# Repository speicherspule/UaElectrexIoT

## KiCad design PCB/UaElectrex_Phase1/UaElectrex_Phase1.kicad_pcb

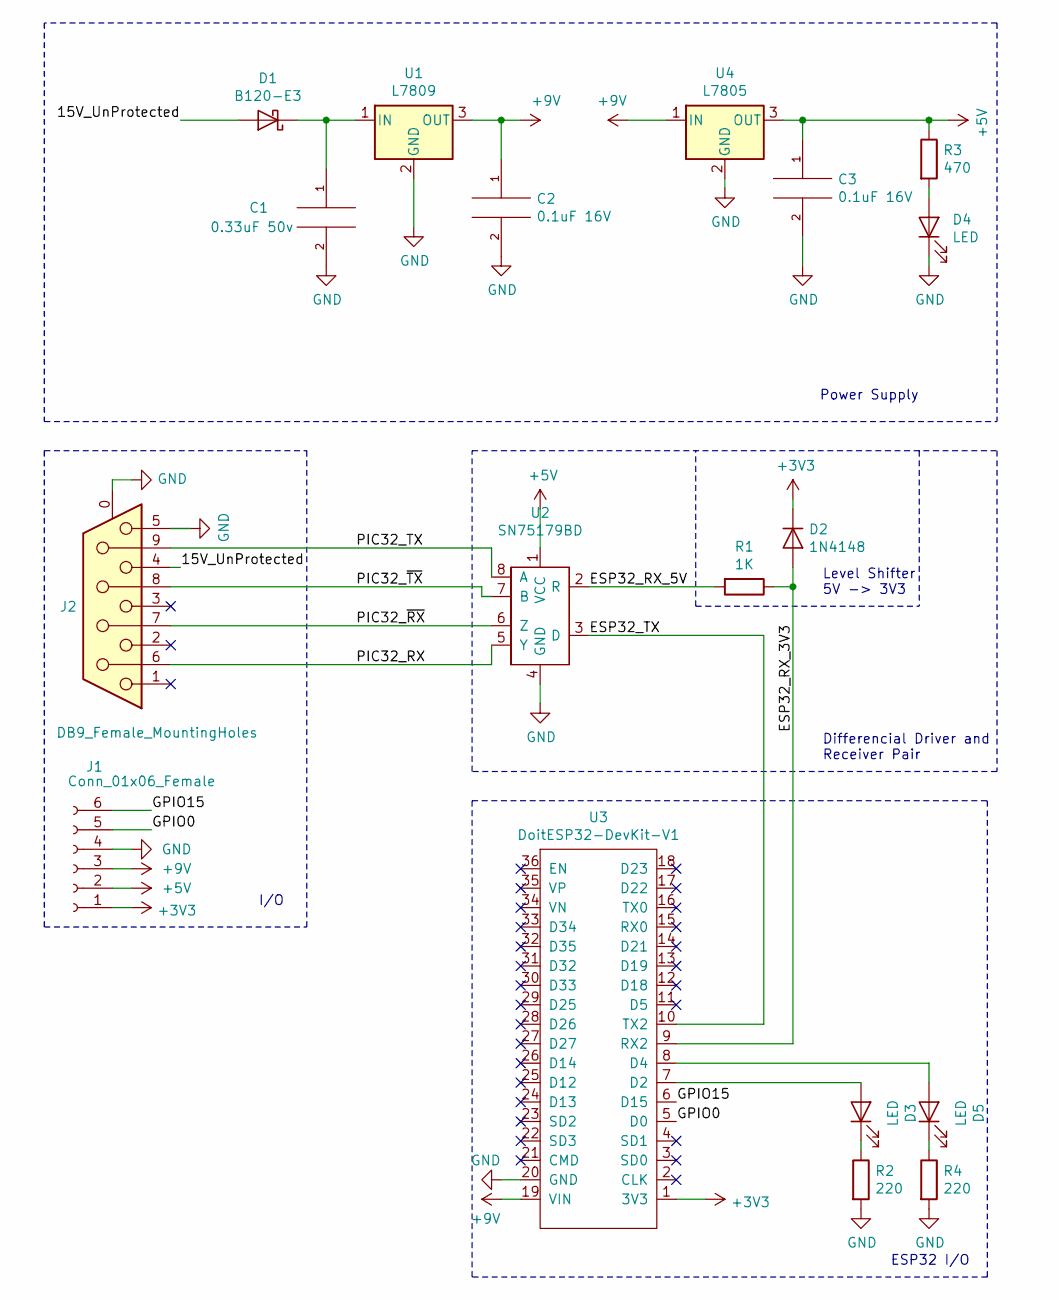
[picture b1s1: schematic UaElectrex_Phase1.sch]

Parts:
C1: 0.33uF 50v; C_0805_2012Metric_Pad1.15x1.40mm_HandSolder
C2, C3: 0.1uF 16V; C_0805_2012Metric_Pad1.15x1.40mm_HandSolder
D1: B120-E3; D_SMA
D2: 1N4148; D_SOD-123
D3, D4, D5: LED; LED_0603_1608Metric_Pad1.05x0.95mm_HandSolder
J1: Conn_01x06_Female; PinSocket_1x06_P2.54mm_Vertical
J2: DB9_Female_MountingHoles; DSUB-9_Female_Horizontal_P2.77x2.84mm_EdgePinOffset4.94mm_H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
R1: 1K; R_0603_1608Metric_Pad1.05x0.95mm_HandSolder
R2, R4: 220; R_0603_1608Metric_Pad1.05x0.95mm_HandSolder
R3: 470; R_0603_1608Metric_Pad1.05x0.95mm_HandSolder
U1: L7809; TO-220-3_Vertical
U2: SN75179BD; SOIC-8
U3: DoitESP32-DevKit-V1; PinSocket_1x18_P2.54mm_Vertical
U4: L7805; TO-220-3_Vertical

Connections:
+3V3: D2.1 (K), J1.1, U3.1 (3V3)
+5V: C3.1, J1.2, R3.1, U2.1 (VCC), U4.3 (OUT)
+9V: C2.1, J1.3, U1.3 (OUT), U3.19 (VIN), U4.1 (IN)
/15V_UnProtected: D1.2 (A), J2.4
/ESP32_RX_3V3: D2.2 (A), R1.1, U3.9 (RX2)
/ESP32_RX_5V: R1.2, U2.2 (R)
/ESP32_TX: U2.3 (D), U3.10 (TX2)
/GPIO0: J1.5, U3.5 (D0)
/GPIO15: J1.6, U3.6 (D15)
/PIC32_RX: J2.6, U2.5 (Y)
/PIC32_TX: J2.9, U2.8 (A)
/PIC32_~RX: J2.7, U2.6 (Z)
/PIC32_~TX: J2.8, U2.7 (B)
GND: C1.2, C2.2, C3.2, D4.1 (K), J1.4, J2.0 (PAD), J2.5, R2.2, R4.2, U1.2 (GND), U2.4 (GND), U3.20 (GND), U4.2 (GND)
unnamed: C1.1, D1.1 (K), U1.1 (IN)
unnamed: D3.1 (K), R2.1
unnamed: D3.2 (A), U3.7 (D2)
unnamed: D4.2 (A), R3.2
unnamed: D5.1 (K), R4.1
unnamed: D5.2 (A), U3.8 (D4)

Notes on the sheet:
Differencial Driver and Receiver Pair
Level Shifter 5V -> 3V3
Power Supply
I/O
ESP32 I/O

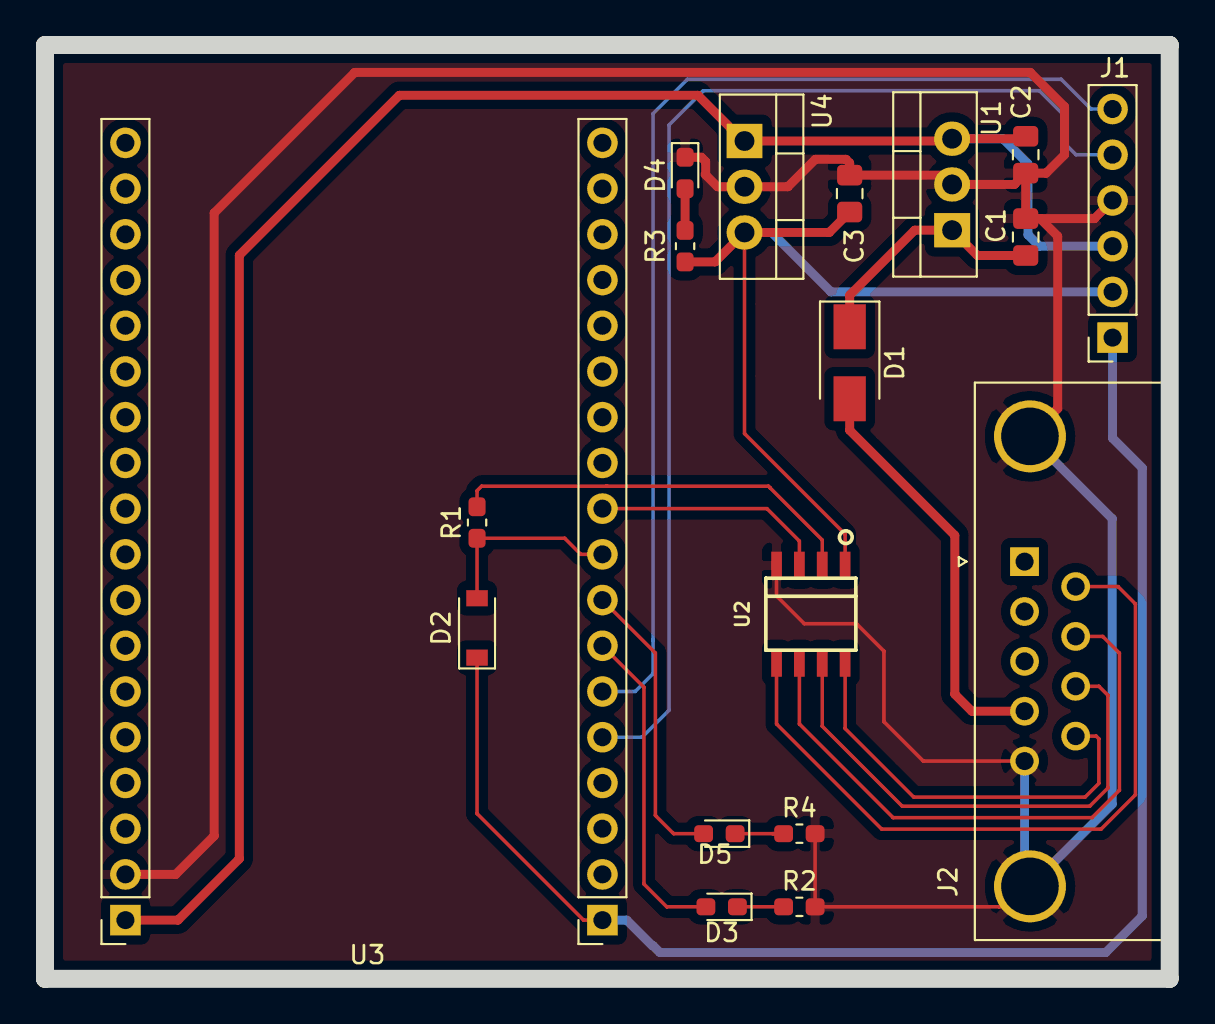
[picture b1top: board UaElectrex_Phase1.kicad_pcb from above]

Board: 2 copper layers, 62.5 x 51.9 mm, 18 parts (0 on the bottom side), 20 nets.

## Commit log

2020-02-03 update code to repository
2020-03-04 last update on html code and back-end code
2020-03-04 added PCB project folder with files for v0 phase 1 PCB
2020-03-04 update gerber files
2020-03-06 add pdfs and images
2020-03-06 add file with external lib
2020-05-26 update both micro code files
2020-06-17 add pic32 uart state machine
2020-06-17 update pic32 uart state machine
2020-06-17 update esp32 for last version
2020-09-22 add webapp source files
2020-10-07 src webapp files
2020-10-07 update pcb to last version
2020-10-07 add esp32 code for phase 2; comunication with firebase
